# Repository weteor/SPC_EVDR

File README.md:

# SPC EVDR
38 key orthogonl keyboard w/ offset spacebar

## Features

- MX w/ hotswap
- encoder (12 mm knob diameter)
- OLED
- Bluetooth and USB connection
- case with optional acrylic accents
- case files are supplied (stl, dxf, as well as the freecad files)
- ZMK firmware support ( on Seeed Xiao SAMD21 or Seeed Xiao BLE )
- QMK firmware support ( on Seeed Xiao RP2040 )
- completely open source, permissive license

## Want one?
All production files you need to build your own board can be found [here](./prod).

Please see the [build instruction](prod/build_guide.md) for a more detailed listing of all things needed.

Gerber files as well as files needed for 3d printing are provided. Please note that the case design that supports the acryl layin may not be SLN printable. Please print them either in resin or nylon. I've used JLCPCBs printing service (black resin) and it turned out very good, so maybe take a look at that option.

### firmware 
The SPC EVDR uses ZMK firmware.

If you prefer the github workflow, you can find the zmk config [here](https://github.com/weteor/SPC_EVDR-Config).

## the rest
Everything in this repository is free to use however you might see fit. If you want to support me and my projects, please consider linking back to this repository if you build/change/use anything. 

If you would like to send me a tip, you could do it [here](https://ko-fi.com/weteor) (Please don't feel like you have to).

### some more images

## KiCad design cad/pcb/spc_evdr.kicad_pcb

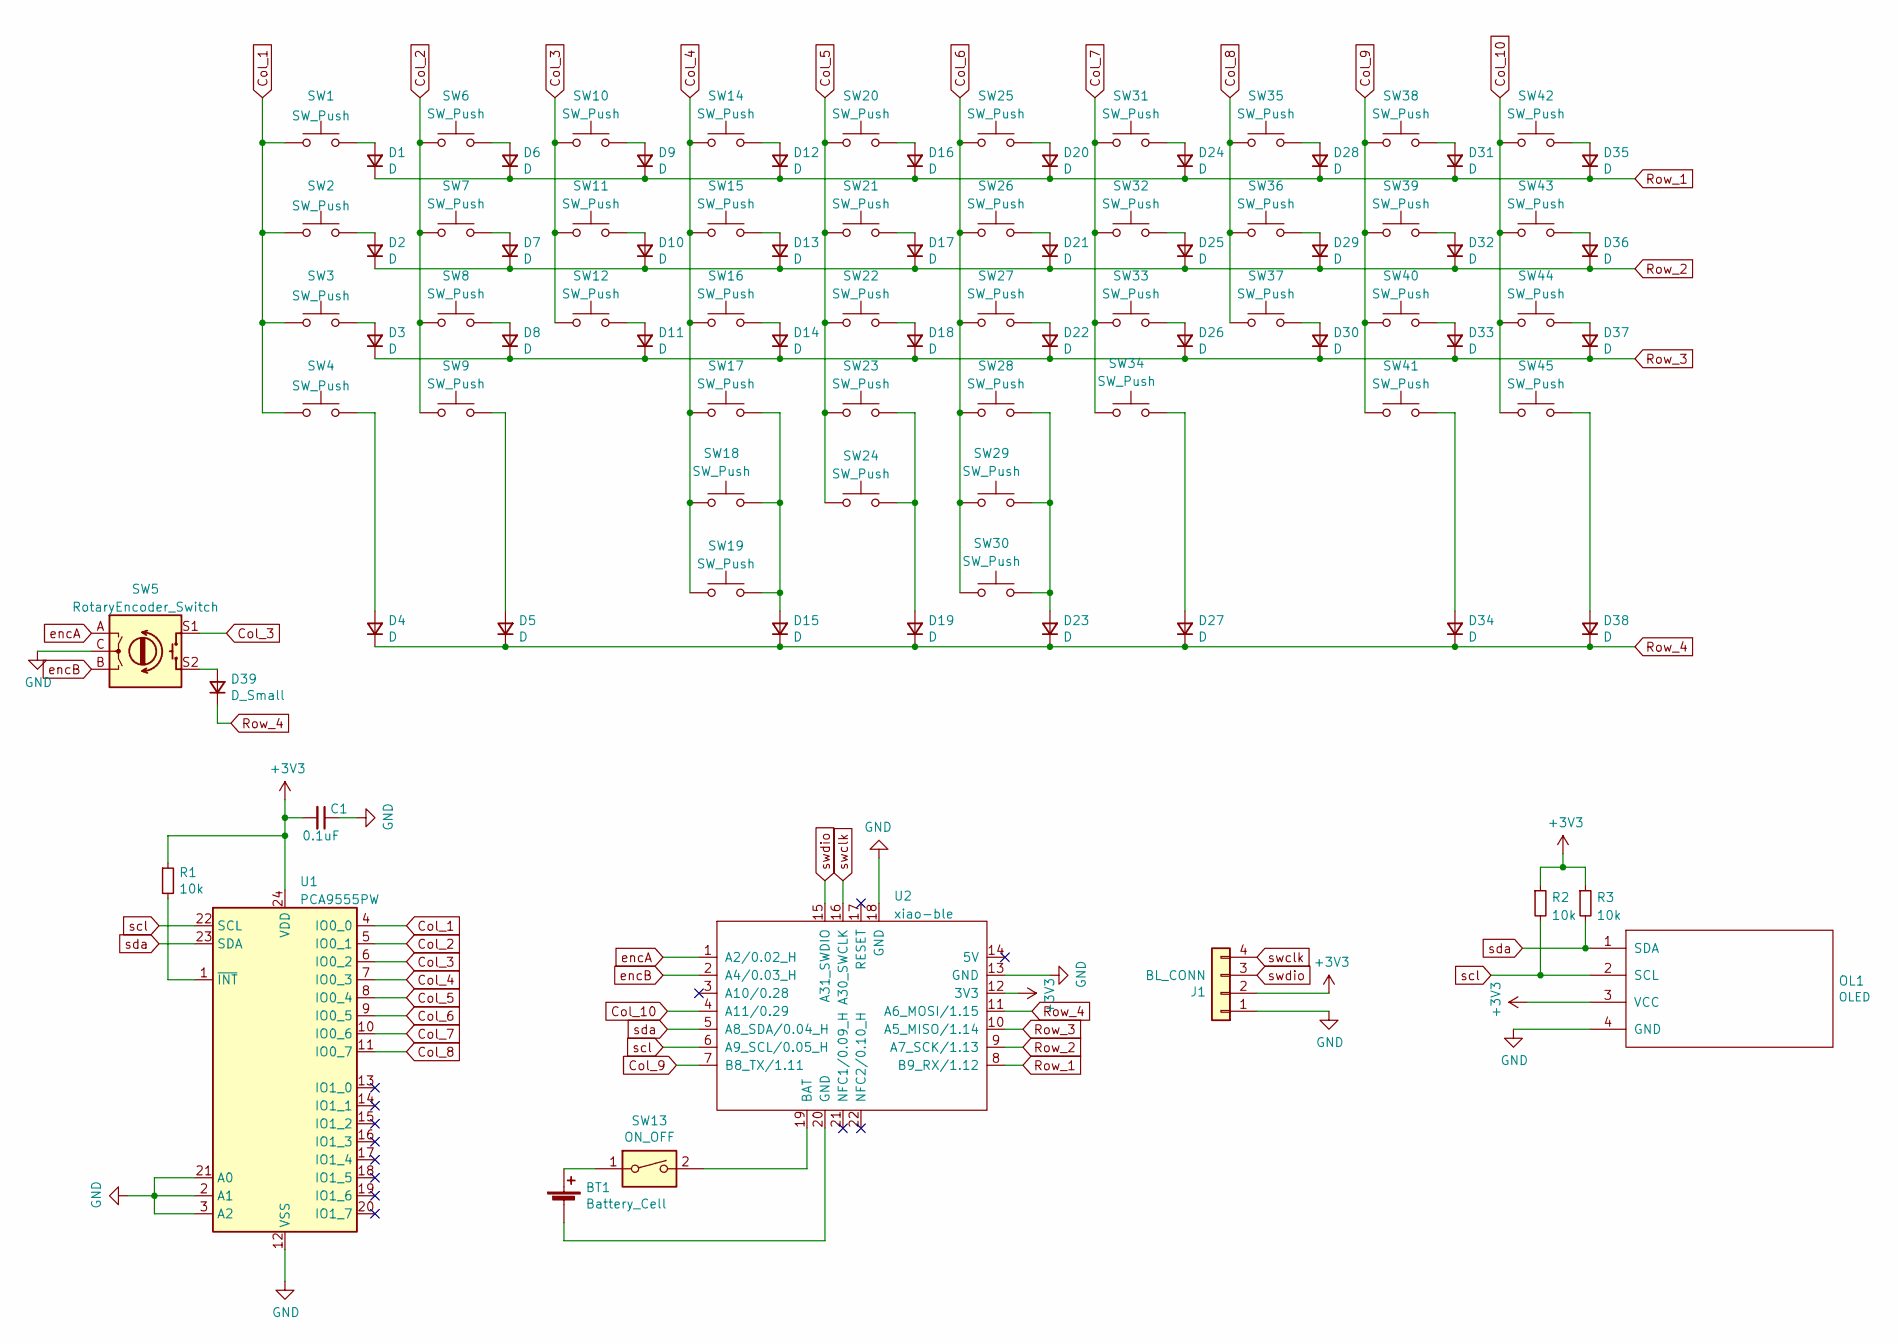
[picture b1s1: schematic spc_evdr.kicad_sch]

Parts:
BT1: Battery_Cell; Molex_PicoBlade_53048-0210_1x02_P1.25mm_Horizontal
C1: 0.1uF; C_0805_2012Metric
D1, D2, D3, D4, D5, D6, D7, D8, D9, D10, D11, D12, D13, D14, D15, D16, D17, D18, D19, D20, D21, D22, D23, D24, D25, D26, D27, D28, D29, D30, D31, D32, D33, D34, D35, D36, D37, D38: D; D_SOD-123
D39: D_Small; D_SOD-123
J1: BL_CONN; PinHeader_1x04_P2.54mm_Vertical
OL1: OLED; OLED_1side
R1, R2, R3: 10k; R_0805_2012Metric
SW1, SW2, SW3, SW4, SW6, SW7, SW8, SW9, SW10, SW11, SW12, SW14, SW15, SW16, SW17, SW20, SW21, SW22, SW25, SW26, SW27, SW31, SW32, SW33, SW34, SW35, SW36, SW37, SW38, SW39, SW40, SW41, SW42, SW43, SW44, SW45: SW_Push; CherryMX_Hotswap
SW5: RotaryEncoder_Switch; RotaryEncoder_Alps_EC11E-Switch_Vertical_H20mm
SW13: ON_OFF; switch_MSK-12C02_smd
SW18, SW29: SW_Push; CherryMX_Hotswap_1.25u
SW19, SW30: SW_Push; CherryMX_Hotswap_2.25u_stabs
SW23, SW28: SW_Push; CherryMX_Hotswap_1.75u
SW24: SW_Push; CherryMX_Hotswap_3u_stabs
U1: PCA9555PW; TSSOP-24_4.4x7.8mm_P0.65mm
U2: xiao-ble; xiao-ble-smd-cutout

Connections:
+3V3: C1.2, J1.2, OL1.3 (VCC), R1.1, R2.1, R3.1, U1.24 (VDD), U2.12 (3V3)
Col_1: SW1.1, SW2.1, SW3.1, SW4.1, U1.4 (IO0_0)
Col_2: SW6.1, SW7.1, SW8.1, SW9.1, U1.5 (IO0_1)
Col_3: SW5.S1, SW10.1, SW11.1, SW12.1, U1.6 (IO0_2)
Col_4: SW14.1, SW15.1, SW16.1, SW17.1, SW18.1, SW19.1, U1.7 (IO0_3)
Col_5: SW20.1, SW21.1, SW22.1, SW23.1, SW24.1, U1.8 (IO0_4)
Col_6: SW25.1, SW26.1, SW27.1, SW28.1, SW29.1, SW30.1, U1.9 (IO0_5)
Col_7: SW31.1, SW32.1, SW33.1, SW34.1, U1.10 (IO0_6)
Col_8: SW35.1, SW36.1, SW37.1, U1.11 (IO0_7)
Col_9: SW38.1, SW39.1, SW40.1, SW41.1, U2.7 (B8_TX/1.11)
Col_10: SW42.1, SW43.1, SW44.1, SW45.1, U2.4 (A11/0.29)
GND: C1.1, J1.1, OL1.4 (GND), SW5.C, U1.2 (A1), U1.3 (A2), U1.12 (VSS), U1.21 (A0), U2.13 (GND), U2.18 (GND)
unnamed: BT1.1 (+), SW13.1
unnamed: BT1.2 (-), U2.20 (GND)
unnamed: D1.2 (A), SW1.2
unnamed: D2.2 (A), SW2.2
unnamed: D3.2 (A), SW3.2
unnamed: D4.2 (A), SW4.2
unnamed: D5.2 (A), SW9.2
unnamed: D6.2 (A), SW6.2
unnamed: D7.2 (A), SW7.2
unnamed: D8.2 (A), SW8.2
unnamed: D9.2 (A), SW10.2
unnamed: D10.2 (A), SW11.2
unnamed: D11.2 (A), SW12.2
unnamed: D12.2 (A), SW14.2
unnamed: D13.2 (A), SW15.2
unnamed: D14.2 (A), SW16.2
unnamed: D15.2 (A), SW17.2, SW18.2, SW19.2
unnamed: D16.2 (A), SW20.2
unnamed: D17.2 (A), SW21.2
unnamed: D18.2 (A), SW22.2
unnamed: D19.2 (A), SW23.2, SW24.2
unnamed: D20.2 (A), SW25.2
unnamed: D21.2 (A), SW26.2
unnamed: D22.2 (A), SW27.2
unnamed: D23.2 (A), SW28.2, SW29.2, SW30.2
unnamed: D24.2 (A), SW31.2
unnamed: D25.2 (A), SW32.2
unnamed: D26.2 (A), SW33.2
unnamed: D27.2 (A), SW34.2
unnamed: D28.2 (A), SW35.2
unnamed: D29.2 (A), SW36.2
unnamed: D30.2 (A), SW37.2
unnamed: D31.2 (A), SW38.2
unnamed: D32.2 (A), SW39.2
unnamed: D33.2 (A), SW40.2
unnamed: D34.2 (A), SW41.2
unnamed: D35.2 (A), SW42.2
unnamed: D36.2 (A), SW43.2
unnamed: D37.2 (A), SW44.2
unnamed: D38.2 (A), SW45.2
unnamed: D39.2 (A), SW5.S2
unnamed: R1.2, U1.1 (~INT)
unnamed: SW13.2, U2.19 (BAT)
Row_1: D1.1 (K), D6.1 (K), D9.1 (K), D12.1 (K), D16.1 (K), D20.1 (K), D24.1 (K), D28.1 (K), D31.1 (K), D35.1 (K), U2.8 (B9_RX/1.12)
Row_2: D2.1 (K), D7.1 (K), D10.1 (K), D13.1 (K), D17.1 (K), D21.1 (K), D25.1 (K), D29.1 (K), D32.1 (K), D36.1 (K), U2.9 (A7_SCK/1.13)
Row_3: D3.1 (K), D8.1 (K), D11.1 (K), D14.1 (K), D18.1 (K), D22.1 (K), D26.1 (K), D30.1 (K), D33.1 (K), D37.1 (K), U2.10 (A5_MISO/1.14)
Row_4: D4.1 (K), D5.1 (K), D15.1 (K), D19.1 (K), D23.1 (K), D27.1 (K), D34.1 (K), D38.1 (K), D39.1 (K), U2.11 (A6_MOSI/1.15)
encA: SW5.A, U2.1 (A2/0.02_H)
encB: SW5.B, U2.2 (A4/0.03_H)
scl: OL1.2 (SCL), R2.2, U1.22 (SCL), U2.6 (A9_SCL/0.05_H)
sda: OL1.1 (SDA), R3.2, U1.23 (SDA), U2.5 (A8_SDA/0.04_H)
swclk: J1.4, U2.16 (A30_SWCLK)
swdio: J1.3, U2.15 (A31_SWDIO)

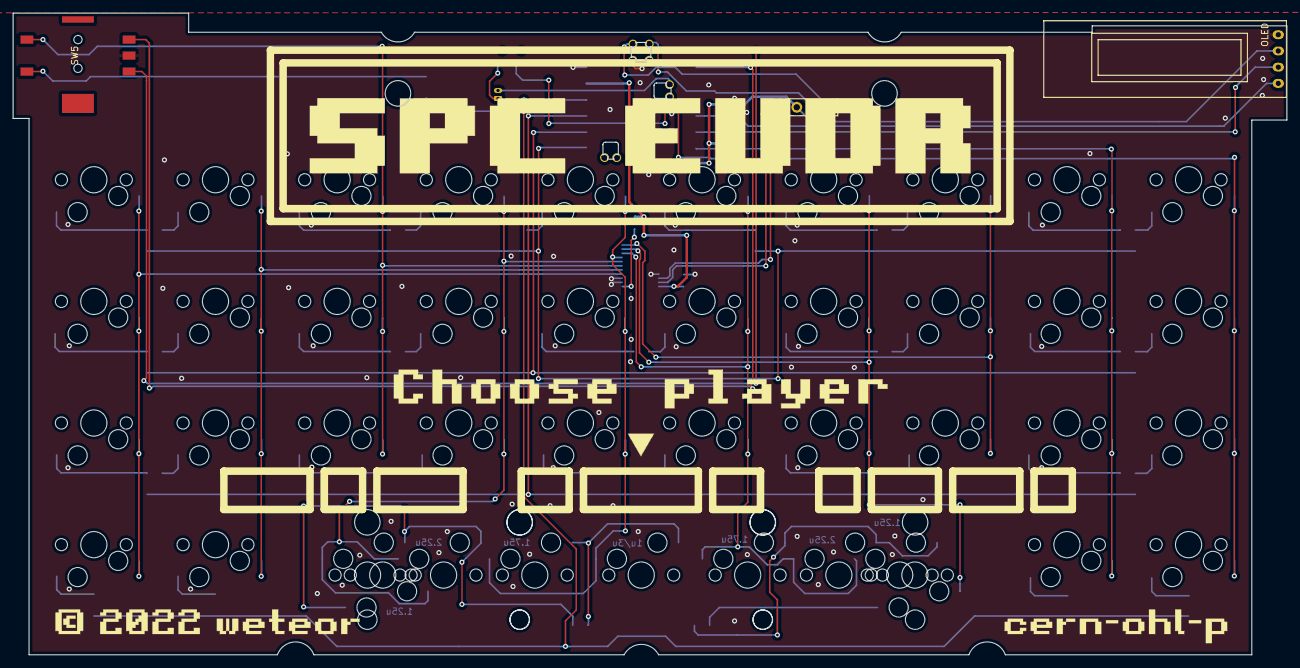
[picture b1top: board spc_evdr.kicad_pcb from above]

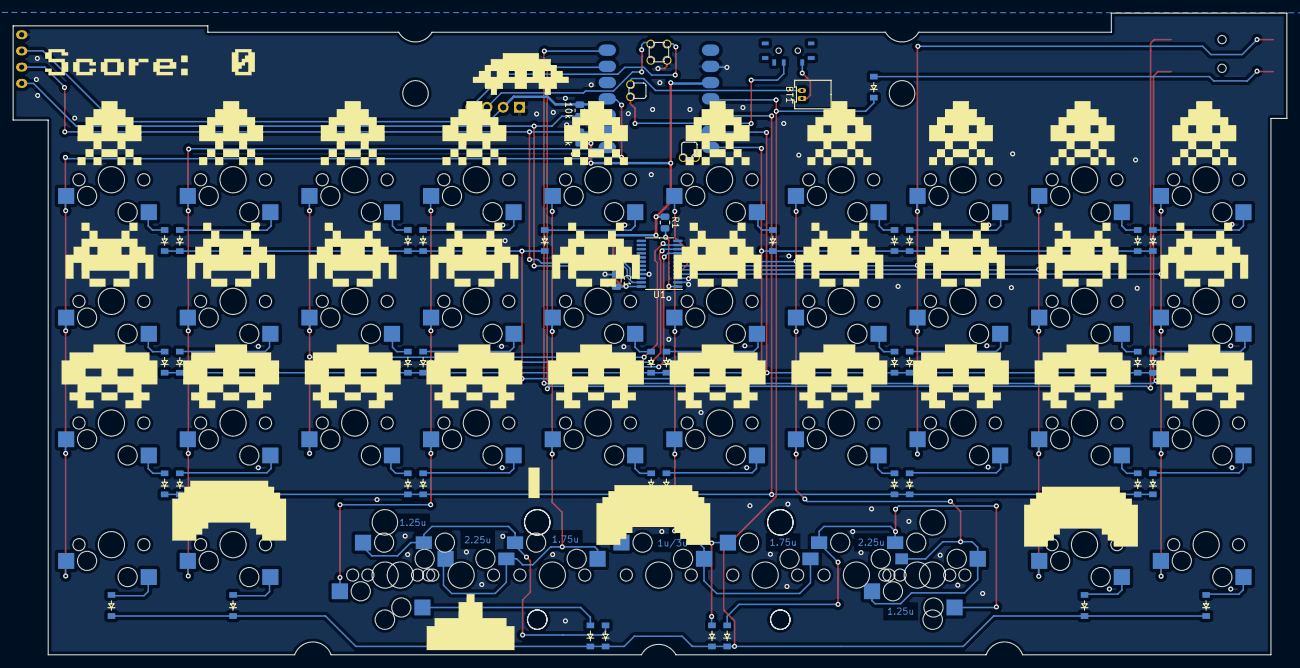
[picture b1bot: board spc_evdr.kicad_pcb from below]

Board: 2 copper layers, 199.5 x 100.5 mm, 93 parts (47 on the bottom side), 65 nets.

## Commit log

2022-09-23 add submodule kleeb
2022-09-23 add mockup case and plate
2022-09-23 move submodules to own directory
2022-09-23 add opl kicad library
2022-09-23 add kbd submodule
2022-09-24 add kicad files, finished functionally
2022-09-24 add border to case
2022-10-24 update pcb files
2022-10-24 update case cad files
2022-10-24 add pcb gerber files
2022-10-24 add case printing and cutting files
2022-10-24 add renders
2022-10-24 add license, readme and build guide
2022-10-24 add top image
2022-10-26 add proto photos
2022-10-26 add images to readme
2023-02-02 Update LICENSE
